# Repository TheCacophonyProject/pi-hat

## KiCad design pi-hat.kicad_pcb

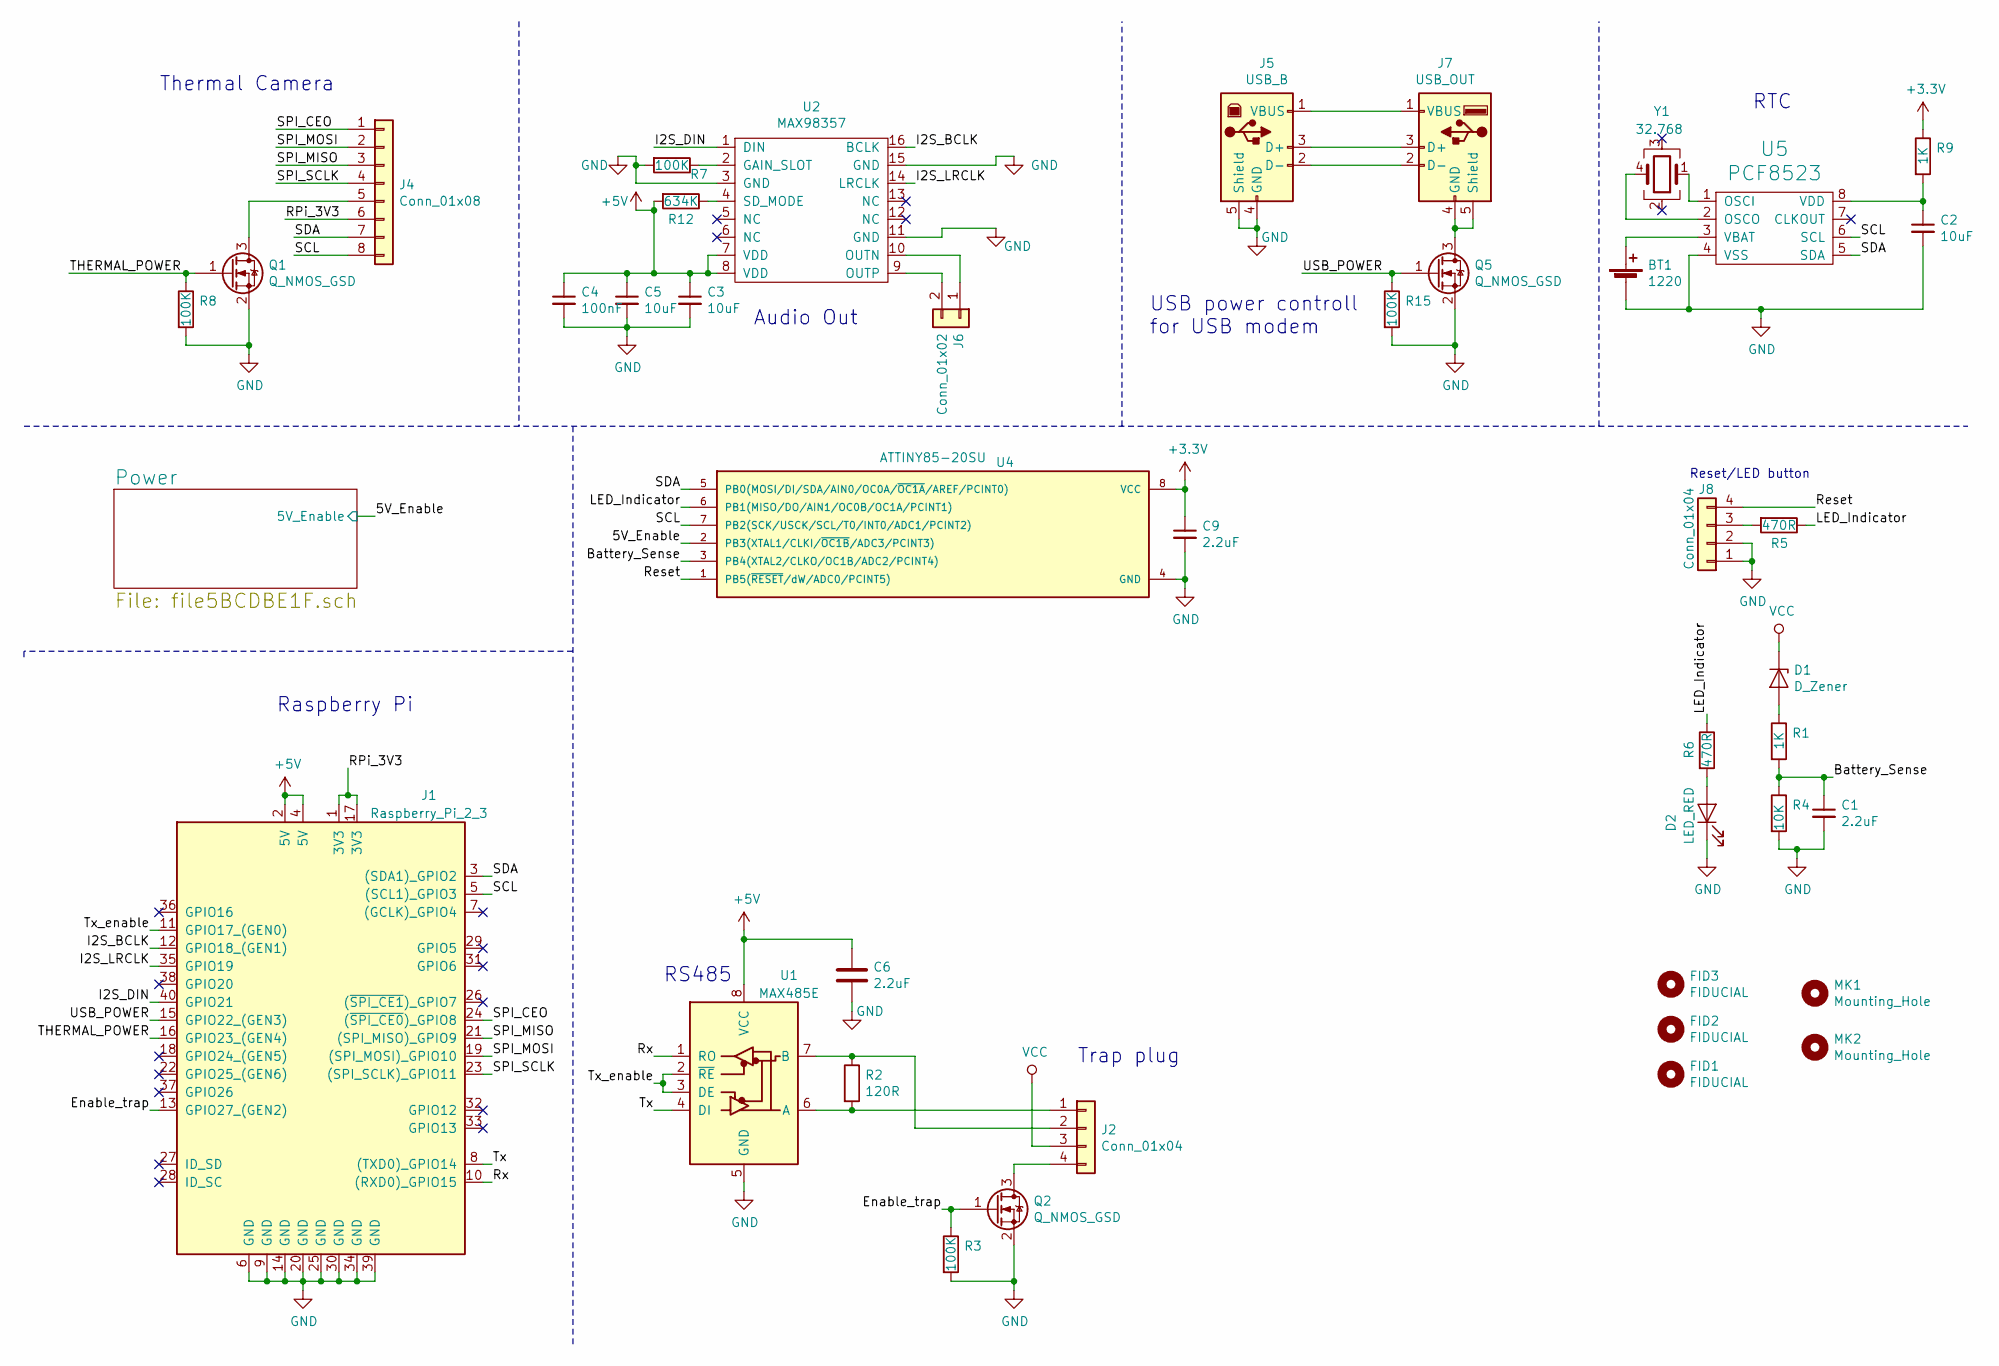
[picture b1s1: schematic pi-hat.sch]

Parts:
BT1: 1220; CR1220; MPN BC501SM; Digikey BC501SM-ND
C1, C6, C9: 2.2uF; C_0603; MPN CL10A225KO8NNNC; Digikey 1276-1040-1-ND
C2, C3, C5: 10uF; C_0805; MPN CL21A106KAYNNNE; Digikey 1276-2891-1-ND
C4: 100nF; C_0805; MPN VJ0805Y104MXXAT; Digikey 720-1756-1-ND
D1: D_Zener; D_SOD-323; MPN MM3Z5V6ST1G; Digikey MM3Z5V6ST1GOSCT-ND
D2: LED_RED; LED_0603; MPN SML-D12U8WT86; Digikey 511-1580-1-ND
FID1, FID2, FID3: FIDUCIAL; Fiducial_1mm_Dia_2.54mm_Outer_CopperTop
J1: Raspberry_Pi_2_3; Pin_Header_Straight_2x20_Pitch2.54mm; MPN ESQ-120-14-G-D; Digikey SAM8767-ND
J2: Conn_01x04; JST_XH_B04B-XH-A_04x2.50mm_Straight; MPN B04B-XASK-1(LF)(SN); Digikey 455-1994-ND
J4: Conn_01x08; JST_XH_B08B-XH-A_08x2.50mm_Straight; MPN B08B-XASK-1(LF)(SN); Digikey 455-1998-ND
J5: USB_B; USB_B_Horizontal; MPN USB-B1HSB6; Digikey ED2983-ND
J6: Conn_01x02; JST_XH_B02B-XH-A_02x2.50mm_Straight; MPN B02B-XASK-1(LF)(SN); Digikey 455-1989-ND
J7: USB_OUT; USB_A_Horizontal; MPN USB-A1HSW6; Digikey ED2989-ND
J8: Conn_01x04; JST_PH_B4B-PH-K_04x2.00mm_Straight; MPN B4B-PH-K-S(LF)(SN); Digikey 455-1706-ND
MK1, MK2: Mounting_Hole; MountingHole_3mm_Pad
Q1, Q2, Q5: Q_NMOS_GSD; SOT-23; MPN AO3414; Digikey 785-1009-1-ND
R1, R9: 1K; R_0603; MPN ERJ-3EKF1001V; Digikey P1.00KHCT-ND
R2: 120R; R_0603; MPN RC1608F121CS; Digikey 1276-4566-1-ND
R3, R7, R8, R15: 100K; R_0603; MPN RR0816P-104-D; Digikey RR08P100KDCT-ND
R4: 10K; R_0603; MPN CRGH0603J10K; Digikey A126394CT-ND
R5, R6: 470R; R_0603; MPN RC0603FR-07470RL; Digikey 311-470HRCT-ND
R12: 634K; R_0603; MPN CRCW0603634KFKEA; Digikey 541-634KHCT-ND
U1: MAX485E; MSOP-8_3x3mm_Pitch0.65mm; MPN MAX3471CUA+; Digikey MAX3471CUA+-ND
U2: MAX98357; QFN-16-1EP_3x3mm_Pitch0.5mm; MPN MAX98357AETE+T; Digikey MAX98357AETE+TCT-ND
U4: ATTINY85-20SU; DIP-8_W7.62mm_Socket; MPN A 08-LC-TT; Digikey AE9986-ND
U5: PCF8523; SOIC-8_3.9x4.9mm_Pitch1.27mm; MPN PCF8523T/1,118; Digikey 568-5306-1-ND
Y1: 32.768; Crystal_SMD_SeikoEpson_MC306-4pin_8.0x3.2mm; MPN ABS25-32.768KHZ-6-T; Digikey 535-10240-1-ND

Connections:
+3V3: C9.1, R9.1, U4.8 (VCC); also elsewhere on the board
+5V: C3.1, C4.1, C5.1, C6.1, J1.2 (5V), J1.4 (5V), R12.2, U1.8 (VCC), U2.7 (VDD), U2.8 (VDD); also elsewhere on the board
/5V_Enable: U4.2 (PB3(XTAL1/CLKI/~OC1B~/ADC3/PCINT3)); also elsewhere on the board
/Battery_Sense: C1.1, R1.2, R4.1, U4.3 (PB4(XTAL2/CLKO/OC1B/ADC2/PCINT4))
/Enable_trap: J1.13 (GPIO27_(GEN2)), Q2.1 (G), R3.1
/I2S_BCLK: J1.12 (GPIO18_(GEN1)), U2.16 (BCLK)
/I2S_DIN: J1.40 (GPIO21), U2.1 (DIN)
/I2S_LRCLK: J1.35 (GPIO19), U2.14 (LRCLK)
/LED_Indicator: R5.1, R6.1, U4.6 (PB1(MISO/DO/AIN1/OC0B/OC1A/PCINT1))
/RPi_3V3: J1.1 (3V3), J1.17 (3V3), J4.6
/Reset: J8.4, U4.1 (PB5(~RESET~/dW/ADC0/PCINT5))
/Rx: J1.10 ((RXD0)_GPIO15), U1.1 (RO)
/SCL: J1.5 ((SCL1)_GPIO3), J4.8, U4.7 (PB2(SCK/USCK/SCL/T0/INT0/ADC1/PCINT2)), U5.6 (SCL)
/SDA: J1.3 ((SDA1)_GPIO2), J4.7, U4.5 (PB0(MOSI/DI/SDA/AIN0/OC0A/~OC1A~/AREF/P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), U5.5 (SDA)
/SPI_CEO: J1.24 ((~SPI_CE0~)_GPIO8), J4.1
/SPI_MISO: J1.21 ((SPI_MISO)_GPIO9), J4.3
/SPI_MOSI: J1.19 ((SPI_MOSI)_GPIO10), J4.2
/SPI_SCLK: J1.23 ((SPI_SCLK)_GPIO11), J4.4
/THERMAL_POWER: J1.16 (GPIO23_(GEN4)), Q1.1 (G), R8.1
/Tx: J1.8 ((TXD0)_GPIO14), U1.4 (DI)
/Tx_enable: J1.11 (GPIO17_(GEN0)), U1.2 (~RE), U1.3 (DE)
/USB_POWER: J1.15 (GPIO22_(GEN3)), Q5.1 (G), R15.1
GND: BT1.2 (-), C1.2, C2.2, C3.2, C4.2, C5.2, C6.2, C9.2, D2.1 (K), J1.6 (GND), J1.9 (GND), J1.14 (GND), J1.20 (GND), J1.25 (GND), J1.30 (GND), J1.34 (GND), J1.39 (GND), J5.4 (GND), J5.5 (Shield), J8.1, J8.2, Q1.2 (S), Q2.2 (S), Q5.2 (S), R3.2, R4.2, R7.2, R8.2, R15.2, U1.5 (GND), U2.3 (GND), U2.11 (GND), U2.15 (GND), U4.4 (GND), U5.4 (VSS); also elsewhere on the board
unnamed: BT1.1 (+), U5.3 (VBAT)
unnamed: C2.1, R9.2, U5.8 (VDD)
unnamed: D1.2 (A), R1.1
unnamed: D2.2 (A), R6.2
unnamed: J2.1, R2.2, U1.6 (A)
unnamed: J2.2, R2.1, U1.7 (B)
unnamed: J2.4, Q2.3 (D)
unnamed: J4.5, Q1.3 (D)
unnamed: J5.1 (VBUS), J7.1 (VBUS)
unnamed: J5.2 (D-), J7.2 (D-)
unnamed: J5.3 (D+), J7.3 (D+)
unnamed: J6.1, U2.10 (OUTN)
unnamed: J6.2, U2.9 (OUTP)
unnamed: J7.4 (GND), J7.5 (Shield), Q5.3 (D)
unnamed: J8.3, R5.2
unnamed: R7.1, U2.2 (GAIN_SLOT)
unnamed: R12.1, U2.4 (SD_MODE)
unnamed: U5.1 (OSCI), Y1.1
unnamed: U5.2 (OSCO), Y1.4
VCC: D1.1 (K), J2.3; also elsewhere on the board

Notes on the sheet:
Raspberry Pi
Audio Out
Thermal Camera
USB power controll for USB modem
Reset/LED button
RTC
RS485
Trap plug

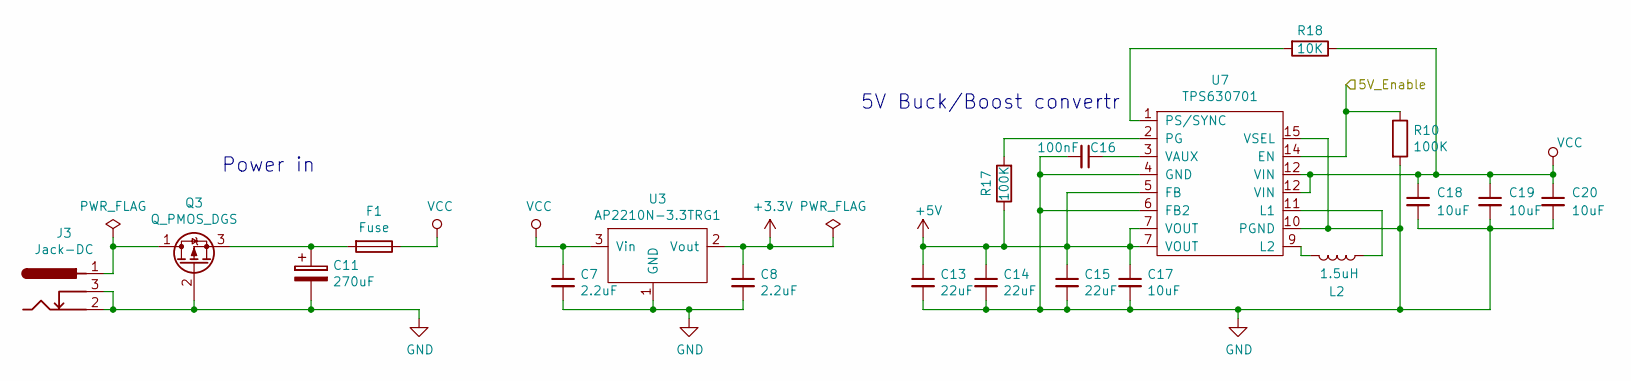
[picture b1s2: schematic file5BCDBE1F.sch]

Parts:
C7, C8: 2.2uF; C_0603; MPN CL10A225KO8NNNC; Digikey 1276-1040-1-ND
C11: 270uF; CP_Radial_D8.0mm_P3.50mm; MPN 25ZLH820MEFC10X20; Digikey 1189-2915-ND
C13, C14, C15: 22uF; C_0805; MPN GRT21BR61E226ME13L; Digikey 490-12389-1-ND
C16: 100nF; C_0805; MPN VJ0805Y104MXXAT; Digikey 720-1756-1-ND
C17, C18: 10uF; C_0603; MPN GRM188R61E106MA73D; Digikey 490-7202-1-ND
C19, C20: 10uF; C_0805; MPN CL21A106KAYNNNE; Digikey 1276-2891-1-ND
F1: Fuse; R_0603_HandSoldering; MPN ERB-RE5R00V; Digikey P15125CT-ND
J3: Jack-DC; BARREL_JACK; MPN PJ-002A; Digikey CP-002A-ND
L2: 1.5uH; ETQP3MxxxKVP; MPN ETQ-P3M1R5KVP; Digikey P19760CT-ND
Q3: Q_PMOS_DGS; IRF9310PbF; MPN IRF9310TRPBF; Digikey IRF9310TRPBFCT-ND
R10, R17: 100K; R_0603; MPN RR0816P-104-D; Digikey RR08P100KDCT-ND
R18: 10K; R_0603; MPN CRGH0603J10K; Digikey A126394CT-ND
U3: AP2210N-3.3TRG1; SOT-23; MPN AP2210N-3.3TRG1; Digikey AP2210N-3.3TRG1DICT-ND
U7: TPS630701; TPS63070; MPN TPS630701RNMT; Digikey 296-44765-1-ND

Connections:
+3V3: C8.1, U3.2 (Vout); also elsewhere on the board
+5V: C13.1, C14.1, C15.1, C17.1, R17.1, U7.5 (FB), U7.7 (VOUT); also elsewhere on the board
/5V_Enable: R10.1, U7.14 (EN); also elsewhere on the board
GND: C7.2, C8.2, C11.2, C13.2, C14.2, C15.2, C16.2, C17.2, C18.2, C19.2, C20.2, J3.2, J3.3, Q3.2 (G), R10.2, U3.1 (GND), U7.4 (GND), U7.6 (FB2), U7.10 (PGND), U7.15 (VSEL); also elsewhere on the board
unnamed: C11.1, F1.2, Q3.3 (S)
unnamed: C16.1, U7.3 (VAUX)
unnamed: J3.1, Q3.1 (D)
unnamed: L2.1, U7.11 (L1)
unnamed: L2.2, U7.9 (L2)
unnamed: R17.2, U7.2 (PG)
unnamed: R18.2, U7.1 (PS/SYNC)
VCC: C7.1, C18.1, C19.1, C20.1, F1.1, R18.1, U3.3 (Vin), U7.12 (VIN); also elsewhere on the board

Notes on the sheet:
5V Buck/Boost convertr
Power in

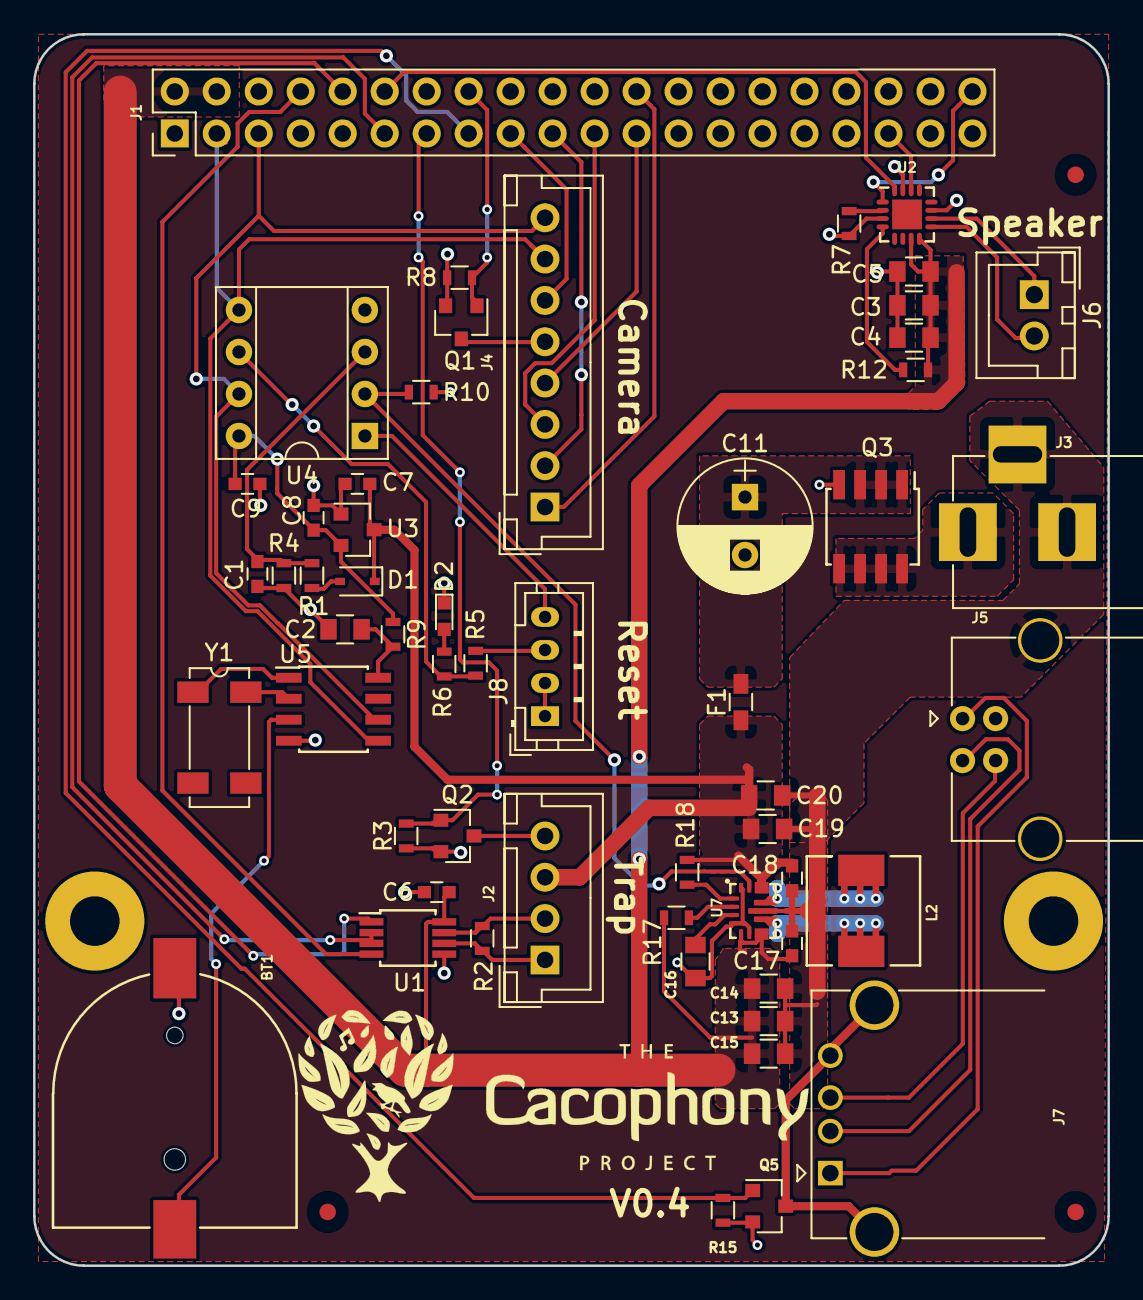
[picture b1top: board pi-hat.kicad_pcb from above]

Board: 2 copper layers, 65.0 x 74.5 mm, 61 parts (0 on the bottom side), 50 nets.

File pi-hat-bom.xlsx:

Generated | Wed 27 Jun 2018 11:49:41 NZST
Ref | Qty | Value | Footprint | Digikey | Digikey2
BT2 | 1 | 1206 | pi-hat-footprints:CR1220 | BC501SM-ND | SY033-ND
C3 C5 C20 C19 C12 | 5 | 10uF | Capacitors_SMD:C_0805_HandSoldering | 490-5523-1-ND
C4 C16 | 2 | 100nF | Capacitors_SMD:C_0805_HandSoldering | 720-1756-1-ND
C11 | 1 | 820uF | Capacitors_THT:CP_Radial_D10.0mm_P5.00mm | 1189-2915-ND
C18 C17 | 2 | 10uF | Capacitors_SMD:C_0603_HandSoldering | 445-11238-1-ND
C13 C14 C15 | 3 | 22uF | Capacitors_SMD:C_0805_HandSoldering | 490-10749-1-ND
C1 C2 | 2 | 1uF | Capacitors_SMD:C_0805_HandSoldering | 732-7625-1-ND
D1 | 1 | LED | LEDs:LED_0603_HandSoldering | 160-1447-1-ND
D2 | 1 | LED_GREEN | LEDs:LED_0603_HandSoldering | 160-1446-1-ND
D4 | 1 | D | Diodes_SMD:D_SOD-323_HandSoldering | 1N4148WXTPMSCT-ND
D3 | 1 | D_Zener | Diodes_SMD:D_SOD-323_HandSoldering | MM3Z4V3BCT-ND
J1 | 1 | Raspberry_Pi_2_3 | Pin_Headers:Pin_Header_Straight_2x20_Pitch2.54mm | SAM8767-ND | S9200-ND
J2 | 1 | Conn_SPI | Connectors_JST:JST_XH_B04B-XH-A_04x2.50mm_Straight | 455-2249-ND
J4 | 1 | Conn_01x08 | Connectors_JST:JST_XH_B08B-XH-A_08x2.50mm_Straight | 455-2251-ND
J7 | 1 | USB_OUT | Connector_USB:USB_A_Horizontal | ED2989-ND
J5 | 1 | USB_B | Connector_USB:USB_B_Horizontal | ED2983-ND
J6 | 1 | Conn_01x02 | Connectors:bornier2 | A98333-ND
J9 | 1 | Conn_01x02 | Connectors_JST:JST_XH_B02B-XH-A_02x2.50mm_Straight | 455-2247-ND
J3 | 1 | Jack-DC | Connectors:BARREL_JACK | CP-002A-ND
L2 | 1 | 1.5uH | pi-hat-footprints:ETQP3MxxxKVP | P19760CT-ND
Q1 Q5 | 2 | Q_NMOS_GDS | TO_SOT_Packages_SMD:SC-59_Handsoldering | 785-1015-1-ND
Q3 | 1 | Q_NMOS_GDS | TO_SOT_Packages_SMD:SOT-223 | NTF3055L108T1GOSCT-ND
R8 R15 R7 R9 R17 | 5 | 100K | Resistors_SMD:R_0603_HandSoldering | CR0603-FX-1003ELFCT-ND
R3 R2 R6 | 3 | 470R | Resistors_SMD:R_0603_HandSoldering | 311-470HRCT-ND
R12 | 1 | 634K | Resistors_SMD:R_0603_HandSoldering | 541-634KHCT-ND
R16 R1 | 2 | 1K | Resistors_SMD:R_0603_HandSoldering | 311-1.0KGRCT-ND
R4 R18 | 2 | 10K | Resistors_SMD:R_0603_HandSoldering | A126331CT-ND
SW1 | 1 | SW_DPST_x2 | switch-footprint:CJS-1200A1 | 563-1021-1-ND
U2 | 1 | MAX98357 | Housings_DFN_QFN:QFN-16-1EP_3x3mm_Pitch0.5mm | MAX98357AETE+TCT-ND
U5 | 1 | ATTINY85-20SU | Housings_DIP:DIP-8_W7.62mm_Socket | AE9986-ND
U7 | 1 | TPS630701 | pi-hat-footprints:TPS63070 | 296-44765-1-ND
U6 | 1 | PCF8523 | Housings_SOIC:SOIC-8_3.9x4.9mm_Pitch1.27mm | 568-5306-1-ND
Y2 | 1 | 32.768 | Crystals:Crystal_SMD_SeikoEpson_MC306-4pin_8.0x3.2mm_HandSoldering | 535-10240-1-ND

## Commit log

2018-07-08 updated pi hat to latest version.
2018-07-08 Added logo
2018-07-17 renamed BOM file
2018-07-20 deleted unused files and tidied up footprint librarys
2018-07-20 deleted unused file
2019-02-15 Added link, MPN, and Digikey number to all parts.
2019-02-15 Added some Seeed OPL parts
2019-03-21 Updated to version 0.3
2019-05-20 Version 4
